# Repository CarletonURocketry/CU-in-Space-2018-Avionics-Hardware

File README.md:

# CU-in-Space-2018-Avionics-Hardware

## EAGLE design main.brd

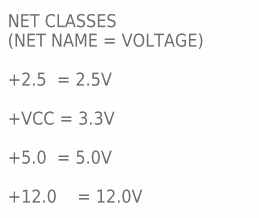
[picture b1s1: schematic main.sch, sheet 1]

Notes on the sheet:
NET CLASSES (NET NAME = VOLTAGE) +2.5 = 2.5V +VCC = 3.3V +5.0 = 5.0V +12.0 = 12.0V

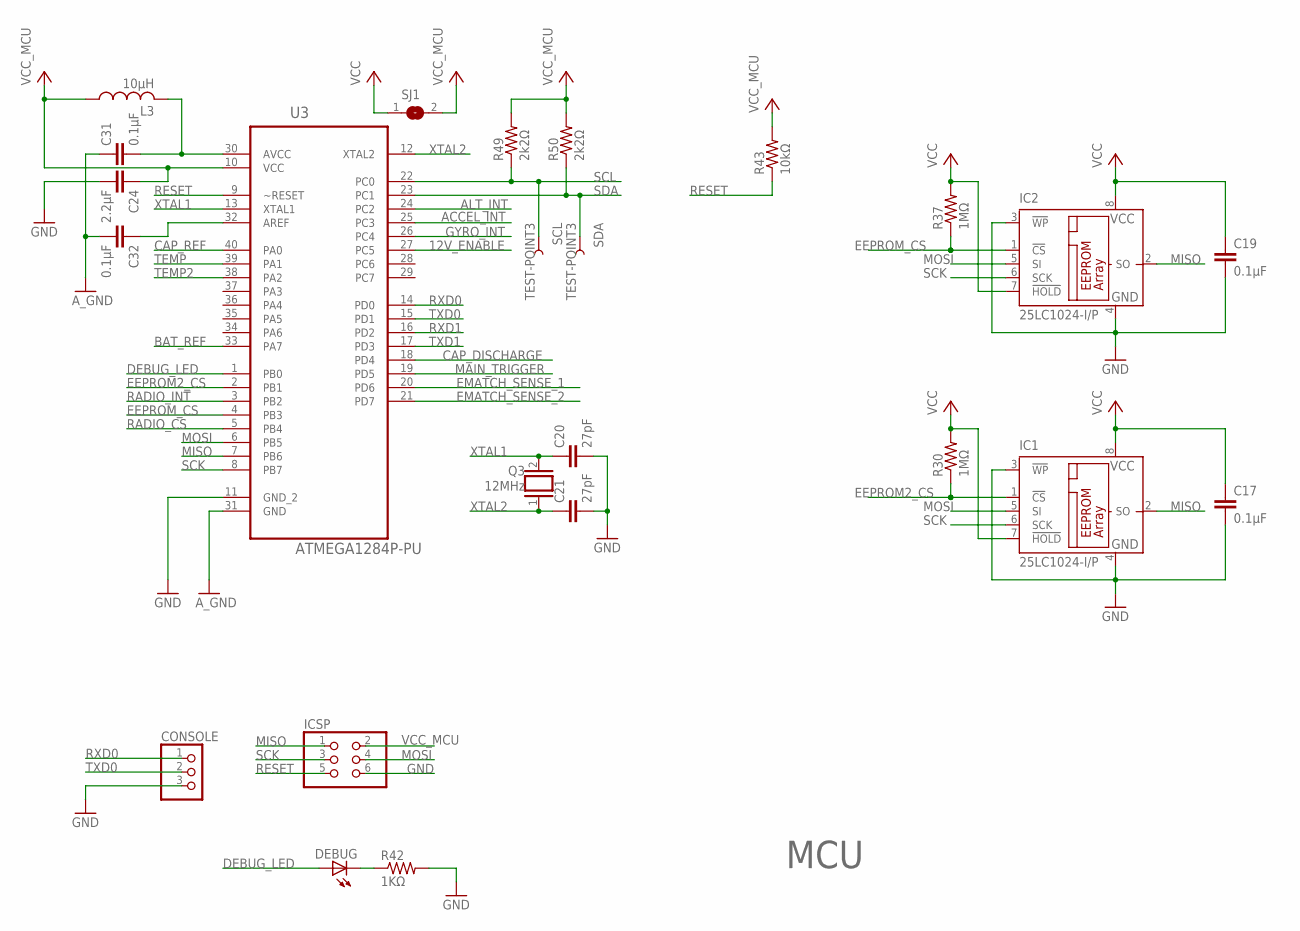
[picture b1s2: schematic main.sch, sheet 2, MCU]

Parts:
C17, C19, C31, C32: 0.1µF; C025-025X050
C20, C21: 27pF; C025-025X050
C24: 2.2µF; C025-025X050
CONSOLE: PINHD-1X3; 1X03
DEBUG: LED5MM
IC1, IC2: 25LC1024-I/P; DIL8
ICSP: PINHD-2X3; 2X03
L3: 10µH; 0207/5V
Q3: 12MHz; QS
R30, R37: 1MΩ; 0207/5V
R42: 1KΩ; 0207/5V
R43: 10kΩ; 0207/5V
R49, R50: 2k2Ω; 0207/5V
SCL: TEST-POINT3; PAD.03X.03
SDA: TEST-POINT3; PAD.03X.03
SJ1: SJ
U3: ATMEGA1284P-PU; DIP254P1524X483-40

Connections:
12V_ENABLE: U3.27 (PC5); also elsewhere on the board
ACCEL_INT: U3.25 (PC3); also elsewhere on the board
ALT_INT: U3.24 (PC2); also elsewhere on the board
AREF: C32.1, U3.32 (AREF)
AVCC: C31.2, L3.2, U3.30 (AVCC); also elsewhere on the board
A_GND: C31.1, C32.2, U3.31 (GND); also elsewhere on the board
BAT_REF: U3.33 (PA7); also elsewhere on the board
CAP_DISCHARGE: U3.18 (PD4); also elsewhere on the board
CAP_REF: U3.40 (PA0); also elsewhere on the board
DEBUG_LED: DEBUG.A, U3.1 (PB0)
EEPROM2_CS: IC1.1 (!CS), R30.1, U3.2 (PB1)
EEPROM_CS: IC2.1 (!CS), R37.1, U3.4 (PB3)
EMATCH_SENSE_1: U3.20 (PD6); also elsewhere on the board
EMATCH_SENSE_2: U3.21 (PD7); also elsewhere on the board
GND: C17.2, C19.2, C20.2, C21.2, C24.2, CONSOLE.3, IC1.3 (!WP), IC1.4 (GND), IC2.3 (!WP), IC2.4 (GND), ICSP.6, R42.2, U3.11 (GND_2); also elsewhere on the board
GYRO_INT: U3.26 (PC4); also elsewhere on the board
MAIN_TRIGGER: U3.19 (PD5); also elsewhere on the board
MISO: IC1.2 (SO), IC2.2 (SO), ICSP.1, U3.7 (PB6); also elsewhere on the board
MOSI: IC1.5 (SI), IC2.5 (SI), ICSP.4, U3.6 (PB5); also elsewhere on the board
unnamed: DEBUG.K (C), R42.1
RADIO_CS: U3.5 (PB4); also elsewhere on the board
RADIO_INT: U3.3 (PB2); also elsewhere on the board
RESET: ICSP.5, R43.1, U3.9 (~RESET)
RXD0: CONSOLE.1, U3.14 (PD0)
RXD1: U3.16 (PD2); also elsewhere on the board
SCK: IC1.6 (SCK), IC2.6 (SCK), ICSP.3, U3.8 (PB7); also elsewhere on the board
SCL: R49.1, SCL.P$1, U3.22 (PC0); also elsewhere on the board
SDA: R50.1, SDA.P$1, U3.23 (PC1); also elsewhere on the board
TEMP: U3.39 (PA1); also elsewhere on the board
TEMP2: U3.38 (PA2); also elsewhere on the board
TXD0: CONSOLE.2, U3.15 (PD1)
TXD1: U3.17 (PD3); also elsewhere on the board
VCC: C17.1, C19.1, IC1.7 (!HOLD), IC1.8 (VCC), IC2.7 (!HOLD), IC2.8 (VCC), R30.2, R37.2, SJ1.1; also elsewhere on the board
VCC_MCU: C24.1, ICSP.2, L3.1, R43.2, R49.2, R50.2, SJ1.2, U3.10 (VCC); also elsewhere on the board
XTAL1: C20.1, Q3.2, U3.13 (XTAL1)
XTAL2: C21.1, Q3.1, U3.12 (XTAL2)

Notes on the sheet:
MCU

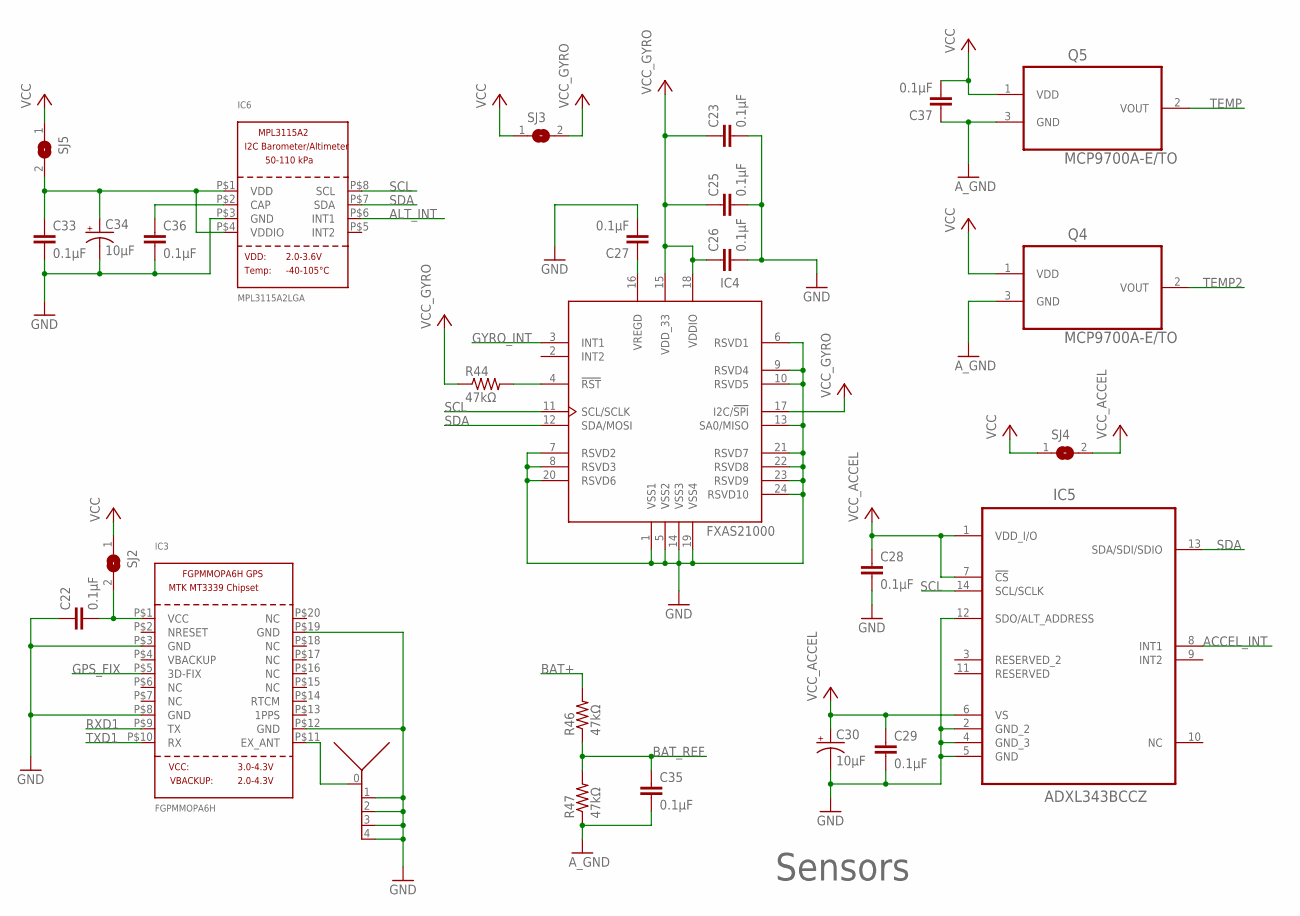
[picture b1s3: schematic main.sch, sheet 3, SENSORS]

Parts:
C22, C23, C25, C26, C27, C28, C29, C33, C35, C36, C37: 0.1µF; C025-025X050
C30, C34: 10µF; E2-5
IC3: FGPMMOPA6H
IC4: FXAS21000; QFN24_0P5_4X4_ASYM_EXP
IC5: ADXL343BCCZ; LGA14R80P1X6_300X500X100
IC6: MPL3115A2LGA; LGA8
Q4, Q5: MCP9700A-E/TO; TO127P254X533-3
R44, R46, R47: 47kΩ; 0207/5V
SJ2, SJ3, SJ4, SJ5: SJ
X1: 132134RP

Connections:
ACCEL_INT: IC5.8 (INT1); also elsewhere on the board
ALT_INT: IC6.P$6 (INT1); also elsewhere on the board
AVCC: C37.2, Q4.1 (VDD), Q5.1 (VDD); also elsewhere on the board
A_GND: C35.2, C37.1, Q4.3 (GND), Q5.3 (GND), R47.1; also elsewhere on the board
BAT+: R46.2; also elsewhere on the board
BAT_REF: C35.1, R46.1, R47.2; also elsewhere on the board
GND: C22.1, C23.2, C25.2, C26.2, C27.2, C28.2, C29.2, C30.-, C33.2, C34.-, C36.2, IC3.P$3 (GND), IC3.P$8 (GND), IC3.P$12 (GND), IC3.P$19 (GND), IC4.1 (VSS1), IC4.5 (VSS2), IC4.6 (RSVD1), IC4.7 (RSVD2), IC4.8 (RSVD3), IC4.9 (RSVD4), IC4.10 (RSVD5), IC4.13 (SA0/MISO), IC4.14 (VSS3), IC4.19 (VSS4), IC4.20 (RSVD6), IC4.21 (RSVD7), IC4.22 (RSVD8), IC4.23 (RSVD9), IC4.24 (RSVD10), IC5.2 (GND_2), IC5.4 (GND_3), IC5.5 (GND), IC5.12 (SDO/ALT_ADDRESS), IC6.P$3 (GND), X1.1 (GND), X1.2 (GND), X1.3 (GND), X1.4 (GND); also elsewhere on the board
GPS_FIX: IC3.P$5 (3D-FIX)
GYRO_INT: IC4.3 (INT1); also elsewhere on the board
unnamed: C27.1, IC4.16 (VREGD)
unnamed: IC4.4 (!RST), R44.2
unnamed: C36.1, IC6.P$2 (CAP)
unnamed: IC3.P$11 (EX_ANT), X1.0 (ANTENNA)
RXD1: IC3.P$9 (TX); also elsewhere on the board
SCL: IC4.11 (SCL/SCLK), IC5.14 (SCL/SCLK), IC6.P$8 (SCL); also elsewhere on the board
SDA: IC4.12 (SDA/MOSI), IC5.13 (SDA/SDI/SDIO), IC6.P$7 (SDA); also elsewhere on the board
TEMP: Q5.2 (VOUT); also elsewhere on the board
TEMP2: Q4.2 (VOUT); also elsewhere on the board
TXD1: IC3.P$10 (RX); also elsewhere on the board
VCC: SJ2.1, SJ3.1, SJ4.1, SJ5.1; also elsewhere on the board
VCC_ACCEL: C28.1, C29.1, C30.+, IC5.1 (VDD_I/O), IC5.6 (VS), IC5.7 (!CS), SJ4.2
VCC_ALT: C33.1, C34.+, IC6.P$1 (VDD), IC6.P$4 (VDDIO), SJ5.2
VCC_GPS: C22.2, IC3.P$1 (VCC), SJ2.2
VCC_GYRO: C23.1, C25.1, C26.1, IC4.15 (VDD_33), IC4.17 (I2C/!SPI), IC4.18 (VDDIO), R44.1, SJ3.2

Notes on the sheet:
Sensors

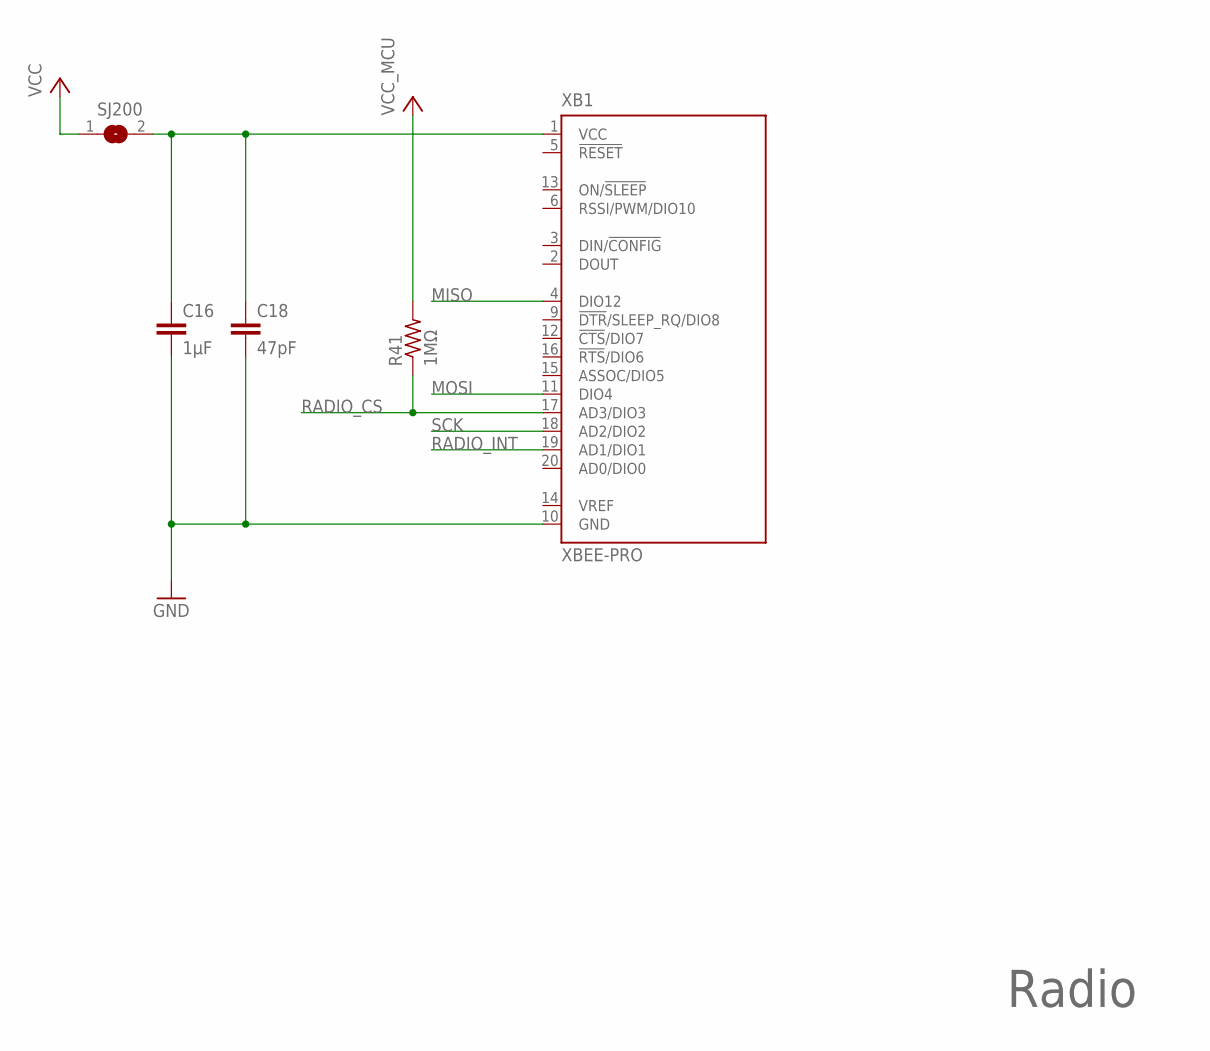
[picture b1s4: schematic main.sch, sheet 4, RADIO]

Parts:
C16: 1µF; C025-025X050
C18: 47pF; C025-025X050
R41: 1MΩ; 0207/5V
SJ200: SJ
XB1: XBEE-PRO

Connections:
GND: C16.2, C18.2, XB1.10 (GND); also elsewhere on the board
MISO: XB1.4 (DIO12); also elsewhere on the board
MOSI: XB1.11 (DIO4); also elsewhere on the board
RADIO_CS: R41.1, XB1.17 (AD3/DIO3); also elsewhere on the board
RADIO_INT: XB1.19 (AD1/DIO1); also elsewhere on the board
SCK: XB1.18 (AD2/DIO2); also elsewhere on the board
VCC: SJ200.1; also elsewhere on the board
VCC_MCU: R41.2; also elsewhere on the board
VCC_XB: C16.1, C18.1, SJ200.2, XB1.1 (VCC)

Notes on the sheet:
Radio

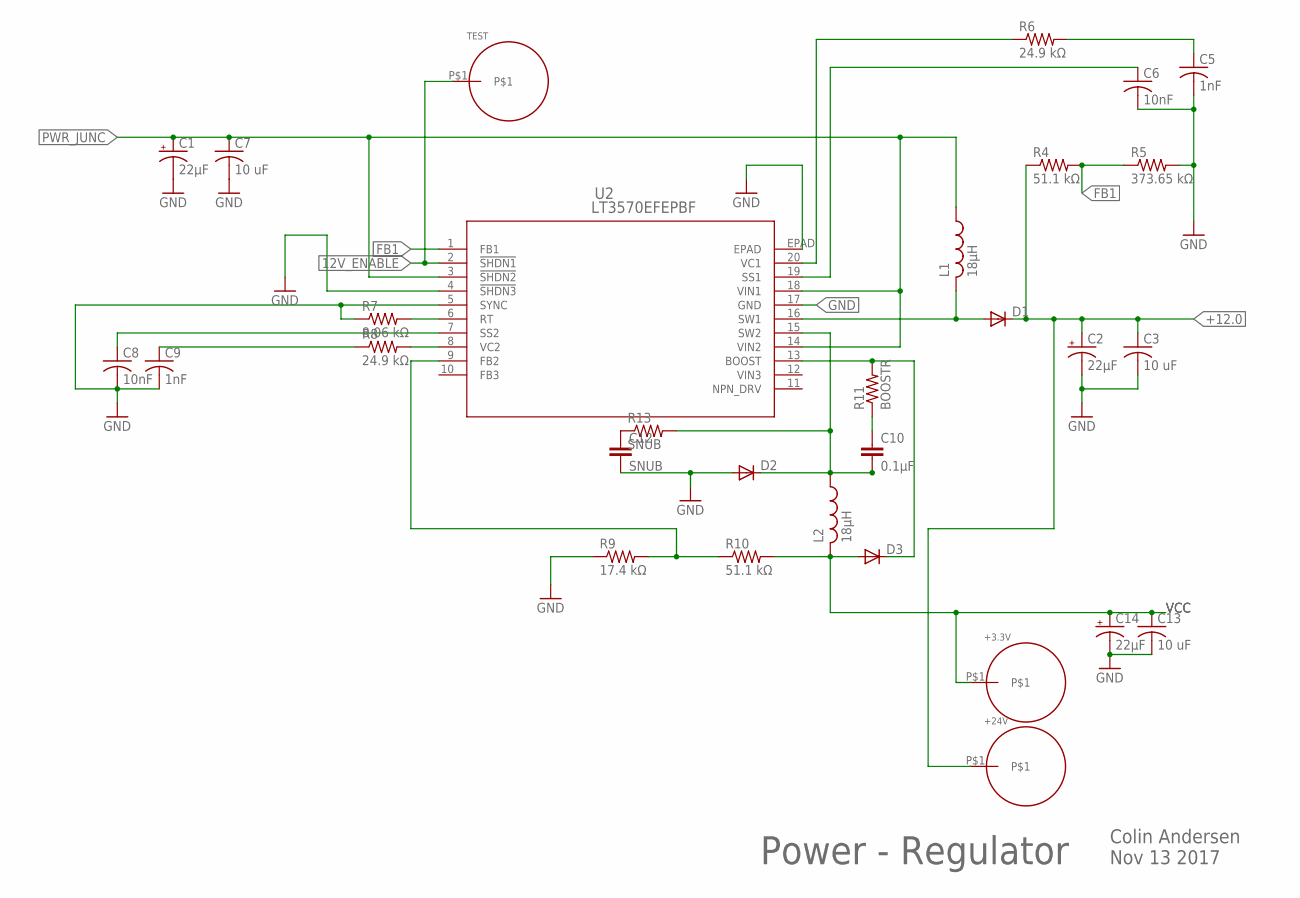
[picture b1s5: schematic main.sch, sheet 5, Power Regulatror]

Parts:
C1, C2, C14: 22µF; 2.5MM_AL_CAP
C3, C7, C13: 10 uF; 2.5MM_CAP
C5, C9: 1nF; 2.5MM_CAP
C6, C8: 10nF; 2.5MM_CAP
C10: 0.1µF; C025-025X050
C12: SNUB; C025-025X050
D1, D2, D3: SB230TA; 11.6MM_D
L1, L2: 18µH; 5.4MM_L
R4, R10: 51.1 kΩ; 0207/5V
R5: 373.65 kΩ; 0207/5V
R6, R8: 24.9 kΩ; 0207/5V
R7: 8.06 kΩ; 0207/5V
R9: 17.4 kΩ; 0207/5V
R11: BOOSTR; 0207/5V
R13: SNUB; 0207/5V
U2: LT3570EFEPBF; TSSOP-20_FE/CB
U$2: +24V; TEST
U$3: +3.3V; TEST
U$5: TEST

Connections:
12V_ENABLE: U2.2 (!SHDN1), U$5.P$1; also elsewhere on the board
+12.0: C2.1 (+), C3.1, D1.1 (C), R4.1, U$2.P$1; also elsewhere on the board
FB1: R4.2, R5.1, U2.1 (FB1)
GND: C1.2 (-), C2.2 (-), C3.2, C5.2, C6.2, C7.2, C8.2, C9.2, C12.2, C13.2, C14.2 (-), D2.2 (A), R5.2, R7.1, R9.1, U2.4 (!SHDN3), U2.5 (SYNC), U2.17 (GND), U2.EPAD; also elsewhere on the board
unnamed: C8.1, U2.7 (SS2)
unnamed: R7.2, U2.6 (RT)
unnamed: R8.2, U2.8 (VC2)
unnamed: D1.2 (A), L1.2, U2.16 (SW1)
unnamed: C5.1, R6.2
unnamed: C9.1, R8.1
unnamed: R6.1, U2.20 (VC1)
unnamed: C6.1, U2.19 (SS1)
unnamed: C10.2, D2.1 (C), L2.1, R13.2, U2.15 (SW2)
unnamed: R9.2, R10.1, U2.9 (FB2)
unnamed: D3.1 (C), R11.2, U2.13 (BOOST)
unnamed: C12.1, R13.1
unnamed: C10.1, R11.1
PWR_JUNC: C1.1 (+), C7.1, L1.1, U2.3 (!SHDN2), U2.14 (VIN2), U2.18 (VIN1); also elsewhere on the board
VCC: C13.1, C14.1 (+), D3.2 (A), L2.2, R10.2, U$3.P$1; also elsewhere on the board

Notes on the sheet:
Power - Regulator
Colin Andersen Nov 13 2017

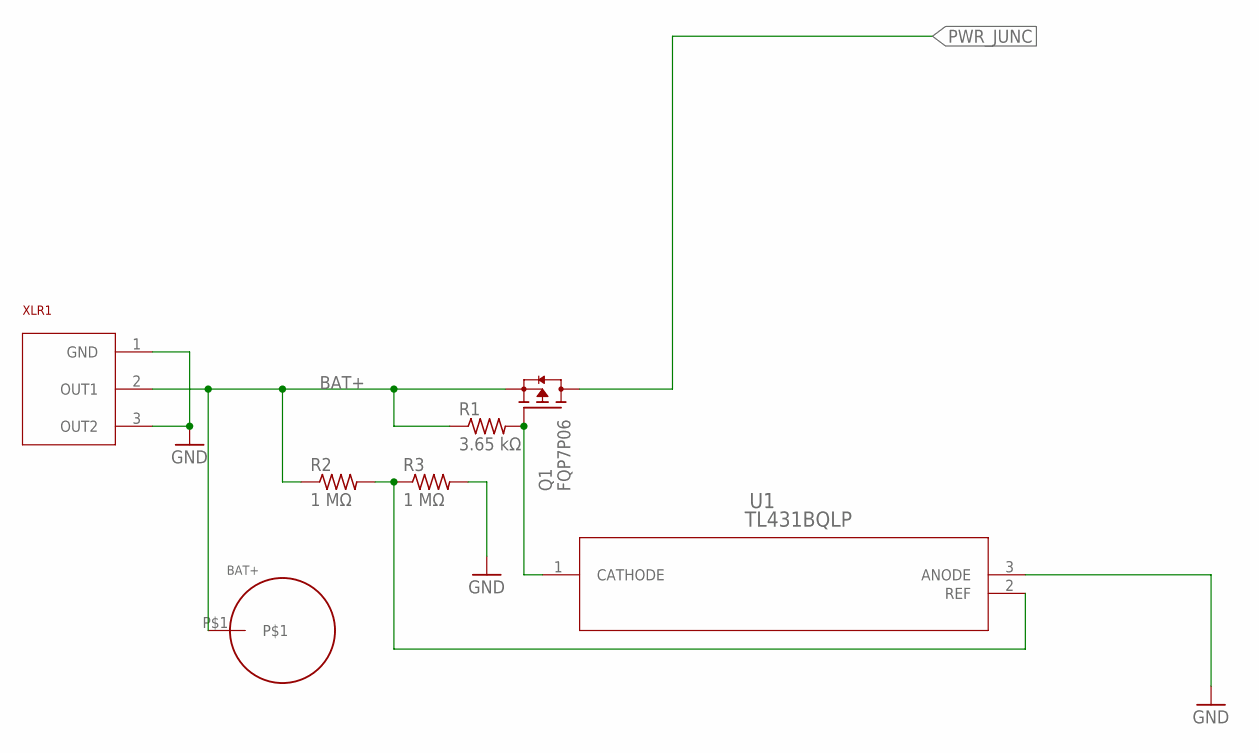
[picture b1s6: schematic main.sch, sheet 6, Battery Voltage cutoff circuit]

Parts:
Q1: FQP7P06; PMOS
R1: 3.65 kΩ; 0207/5V
R2, R3: 1 MΩ; 0207/5V
U1: TL431BQLP; LP3
U$1: BAT+; TEST
XLR1: NC3FAH1

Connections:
BAT+: Q1.3 (S), R1.1, R2.1, U$1.P$1, XLR1.2 (OUT1); also elsewhere on the board
GND: R3.2, U1.3 (ANODE), XLR1.1 (GND), XLR1.3 (OUT2); also elsewhere on the board
unnamed: Q1.1 (G), R1.2, U1.1 (CATHODE)
unnamed: R2.2, R3.1, U1.2 (REF)
PWR_JUNC: Q1.2 (D); also elsewhere on the board

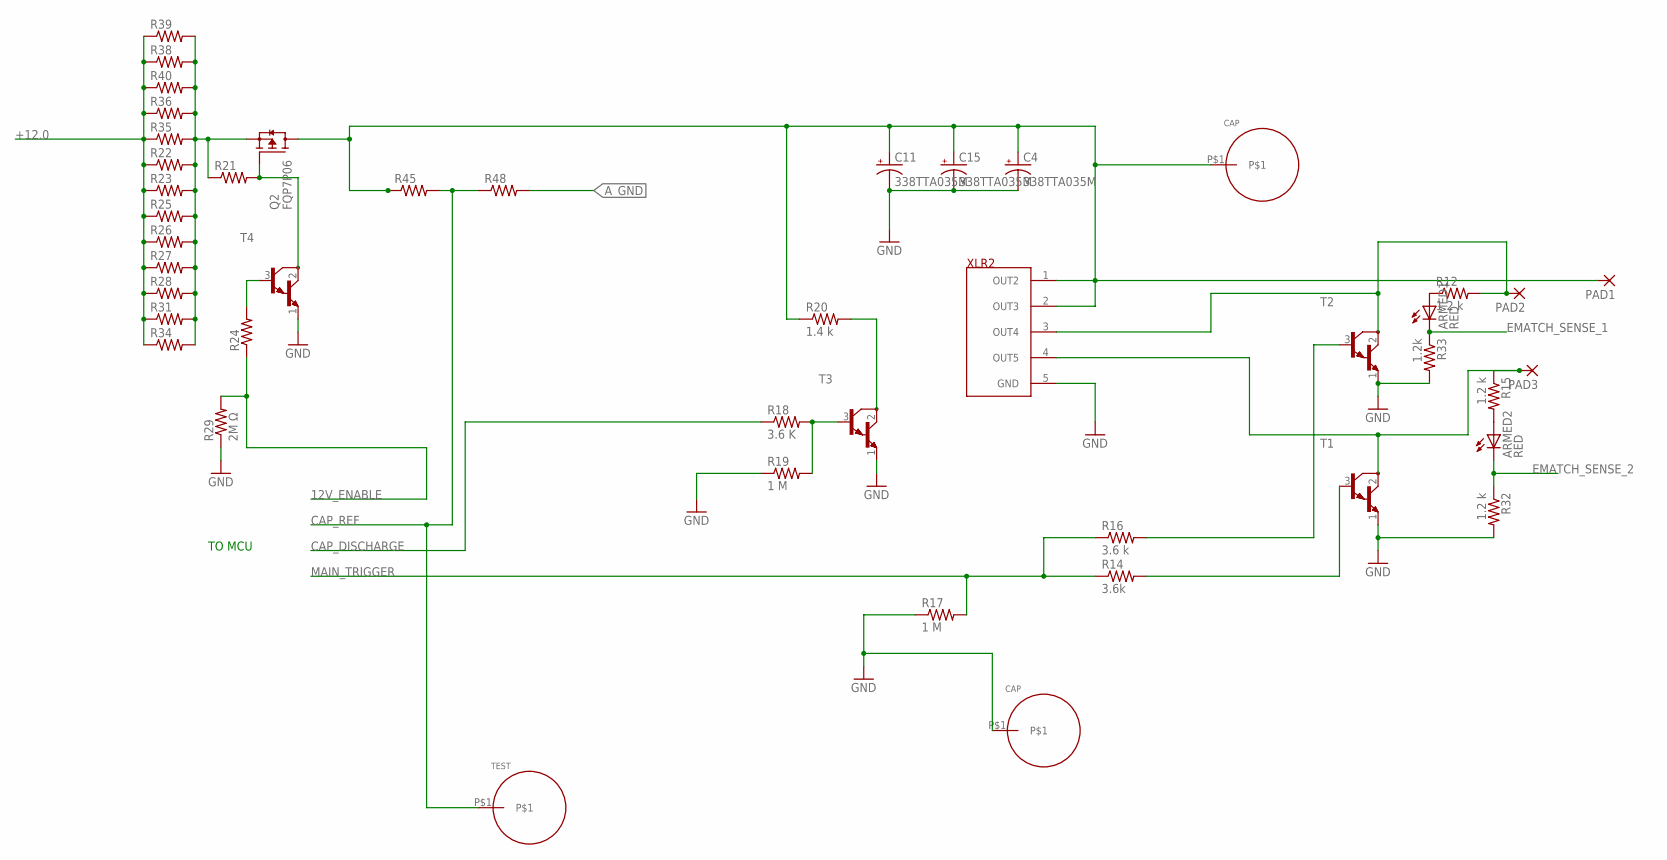
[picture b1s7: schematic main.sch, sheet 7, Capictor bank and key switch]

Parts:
ARMED1, ARMED2: RED; LED5MM
C4, C11, C15: 338TTA035M
PAD1, PAD2, PAD3: CRIMP; 3,81/1,4
Q2: FQP7P06; PMOS
R12, R15, R32: 1.2 k; 0207/5V
R14: 3.6k; 0207/5V
R16: 3.6 k; 0207/5V
R17, R19: 1 M; 0207/5V
R18: 3.6 K; 0207/5V
R20: 1.4 k; 0207/5V
R21, R22, R23, R24, R25, R26, R27, R28, R31, R34, R35, R36, R38, R39, R40, R45, R48: R-US_0207/5V; 0207/5V
R29: 2M Ω; 0207/5V
R33: 1.2k; 0207/5V
T1, T2, T3, T4: -NPN_DARL-; NPNDARL
U$4, U$6: CAP; TEST
U$7: TEST
XLR2: NC5FAH

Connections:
12V_ENABLE: R24.1, R29.2; also elsewhere on the board
+12.0: R22.1, R23.1, R25.1, R26.1, R27.1, R28.1, R31.1, R34.1, R35.1, R36.1, R38.1, R39.1, R40.1; also elsewhere on the board
A_GND: R48.2; also elsewhere on the board
CAP_DISCHARGE: R18.1; also elsewhere on the board
CAP_REF: R45.2, R48.1, U$7.P$1; also elsewhere on the board
EMATCH_SENSE_1: ARMED1.K (C), R33.1; also elsewhere on the board
EMATCH_SENSE_2: ARMED2.K (C), R32.1; also elsewhere on the board
GND: C4.-, C11.-, C15.-, R17.1, R19.1, R29.1, R32.2, R33.2, T1.1 (E), T2.1 (E), T3.1 (E), T4.1 (E), U$4.P$1, XLR2.5 (GND); also elsewhere on the board
MAIN_TRIGGER: R14.1, R16.1, R17.2; also elsewhere on the board
unnamed: Q2.3 (S), R21.1, R22.2, R23.2, R25.2, R26.2, R27.2, R28.2, R31.2, R34.2, R35.2, R36.2, R38.2, R39.2, R40.2
unnamed: Q2.1 (G), R21.2, T4.2 (C)
unnamed: R20.2, T3.2 (C)
unnamed: R24.2, T4.3 (B)
unnamed: PAD3.1, R15.1, T1.2 (C), XLR2.4 (OUT5)
unnamed: PAD2.1, R12.2, T2.2 (C), XLR2.3 (OUT4)
unnamed: R16.2, T2.3 (B)
unnamed: R14.2, T1.3 (B)
unnamed: C4.+, C11.+, C15.+, PAD1.1, Q2.2 (D), R20.1, R45.1, U$6.P$1, XLR2.1 (OUT2), XLR2.2 (OUT3)
unnamed: R18.2, R19.2, T3.3 (B)
unnamed: ARMED2.A, R15.2
unnamed: ARMED1.A, R12.1

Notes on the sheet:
TO MCU

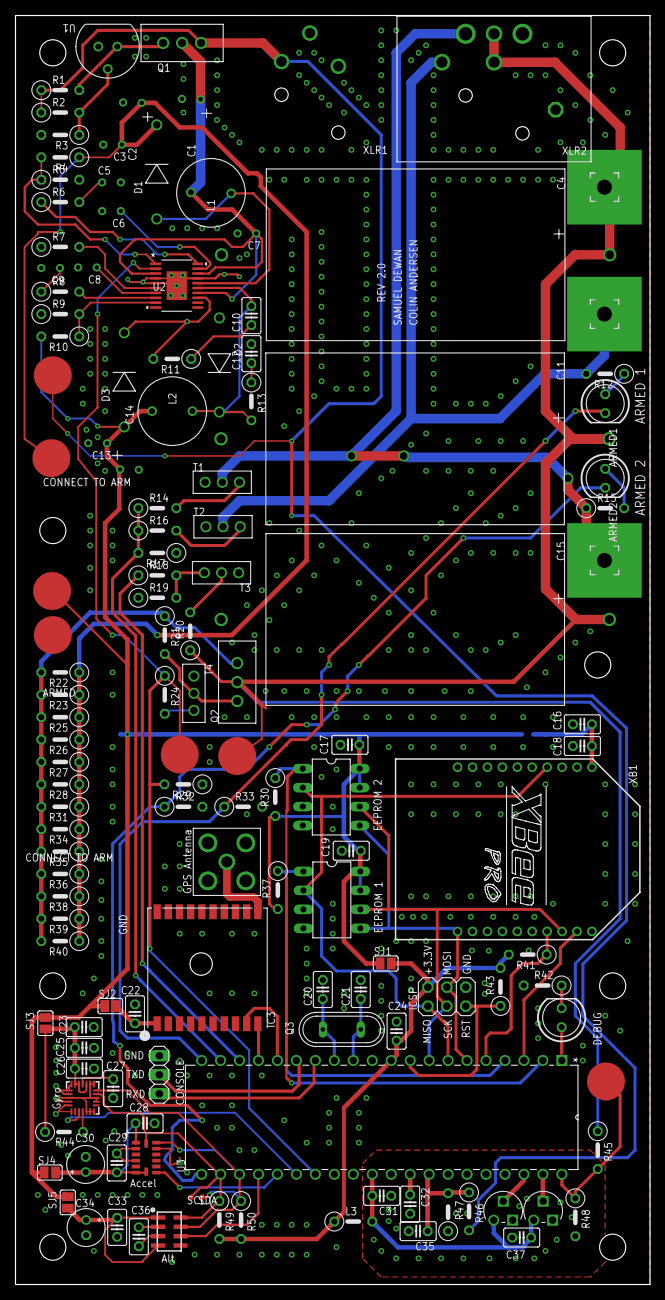
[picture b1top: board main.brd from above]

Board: 2 copper layers, 85.0 x 170.0 mm, 138 parts (1 on the bottom side), 76 nets.

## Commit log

2017-10-28 Added .gitignore
2017-10-28 Added datasheets for most components
2017-10-28 Added rough schematic, board and libraries.
2017-10-31 Added datasheet for XBee
2017-11-02 Added datasheet for MCP9700A temperature sensor and added ambient temperature sensor to schematic.
2017-11-02 Replaced datasheet for ATMega1284p with more recent version.
2017-11-02 Added high value pullups to SPI CS pins to avoid problems during programming
2017-11-03 Added PDF with description of the command format for the GPS module.
2017-11-13 Voltage Regulator added
2017-11-21 Mostly routed
2017-11-23 Power_Fixed
2017-11-23 Updated Datasheets
2018-01-20 Added MCU, Sensors and Radios
2018-02-01 Finished Power bank
    Finished Power bank.
    To do:
    Key switch
    Short circuit protection (PTCs)
2018-02-01 Added more
2018-02-01 Added terminal pads
2018-02-01 Added Pads
2018-02-03 Changed armed sense so that the pin is pulled low when armed and added resistor for armed LED.
2018-02-03 Fixed ERC errors and renumbered all components.
2018-03-30 Relayed-out digital section.
2018-04-02 panannnananael
    pannel
2018-04-02 SPELLING
2018-04-02 Isolation slots

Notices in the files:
parts and their libraries:
SparkFun-Connectors: Licensing: Creative Commons ShareAlike 4.0 International - https://creativecommons.org/licenses/by-sa/4.0
